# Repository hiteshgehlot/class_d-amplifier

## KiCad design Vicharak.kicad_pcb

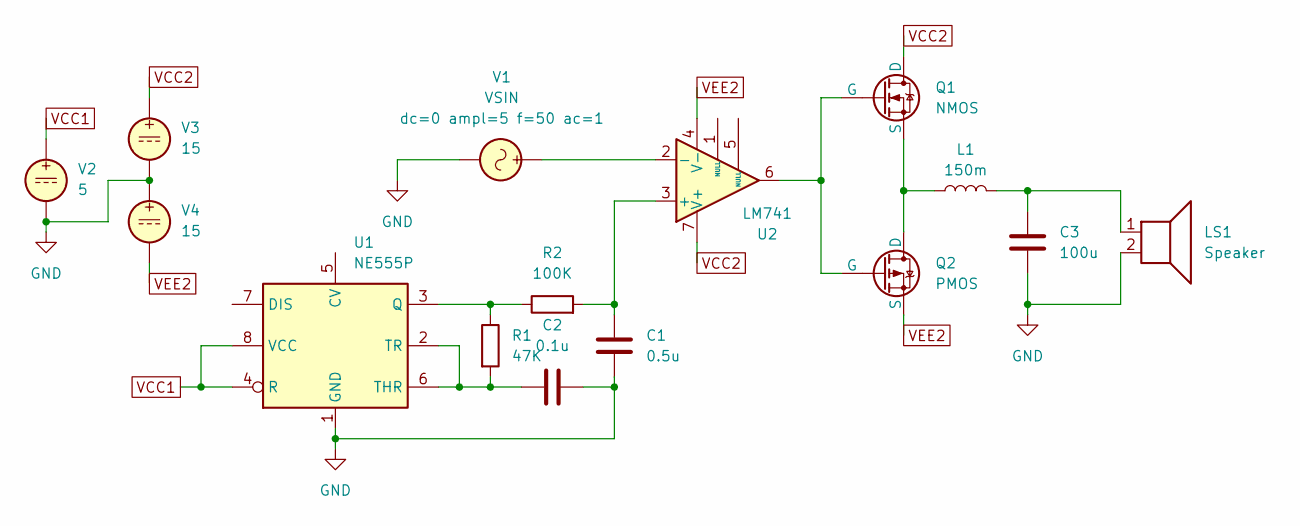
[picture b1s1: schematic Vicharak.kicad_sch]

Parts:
C1: 0.5u; C_Radial_D5.0mm_H5.0mm_P2.00mm
C2: 0.1u; C_Radial_D5.0mm_H5.0mm_P2.00mm
C3: 100u; C_Radial_D8.0mm_H7.0mm_P3.50mm
L1: 150m; L_Axial_L13.0mm_D4.5mm_P15.24mm_Horizontal_Fastron_HCCC
LS1: Speaker; PinSocket_1x02_P2.00mm_Vertical
Q1: NMOS; TO-92L_Inline_Wide
Q2: PMOS; TO-92L_Inline_Wide
R1: 47K; R_Axial_DIN0207_L6.3mm_D2.5mm_P7.62mm_Horizontal
R2: 100K; R_Axial_DIN0207_L6.3mm_D2.5mm_P7.62mm_Horizontal
U1: NE555P; DIP-8_W7.62mm_LongPads
U2: LM741; DIP-8_W7.62mm_LongPads
V1: VSIN; PinSocket_1x02_P2.00mm_Vertical
V2: 5; PinSocket_1x02_P2.00mm_Vertical
V3, V4: 15; PinSocket_1x02_P2.00mm_Vertical

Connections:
GND: C1.2, C2.1, C3.2, LS1.2, U1.1 (GND), V1.2, V2.2, V3.2, V4.1
unnamed: C3.1, L1.2, LS1.1
unnamed: Q1.2 (G), Q2.2 (G), U2.6
unnamed: L1.1, Q1.3 (S), Q2.1 (D)
unnamed: R1.1, R2.1, U1.3 (Q)
unnamed: C2.2, R1.2, U1.2 (TR), U1.6 (THR)
unnamed: C1.1, R2.2, U2.3 (+)
unnamed: U2.2 (-), V1.1
VCC1: U1.4 (R), U1.8 (VCC), V2.1
VCC2: Q1.1 (D), U2.7 (V+), V3.1
VEE2: Q2.3 (S), U2.4 (V-), V4.2

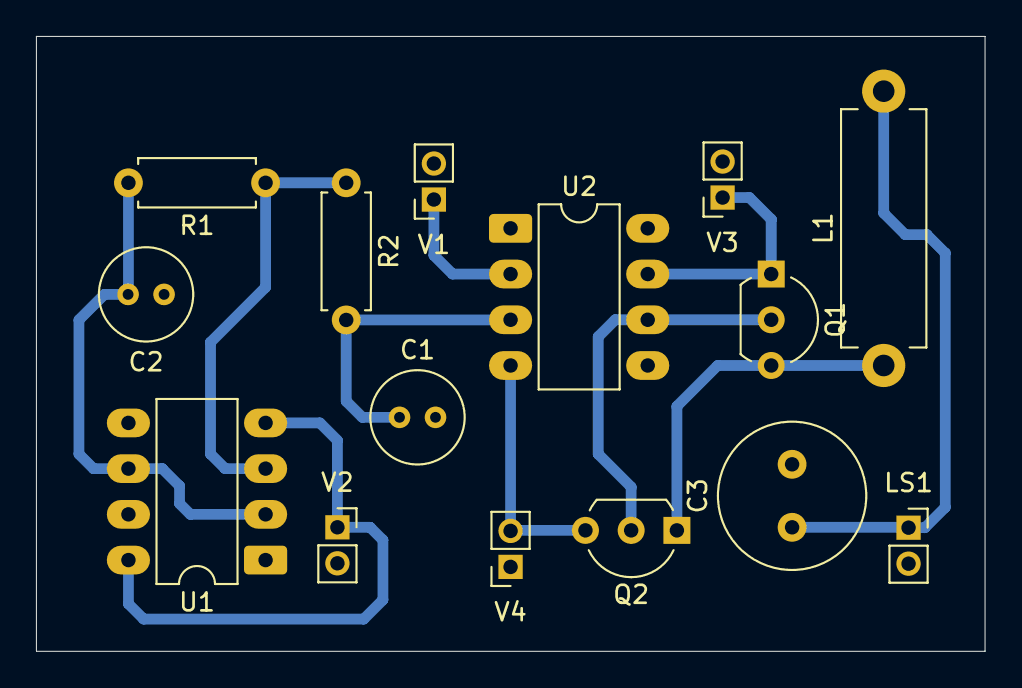
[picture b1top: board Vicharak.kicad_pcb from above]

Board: 2 copper layers, 52.7 x 34.2 mm, 15 parts (0 on the bottom side), 11 nets.
